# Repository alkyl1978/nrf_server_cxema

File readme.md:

печатная плата stelaris модуль с nrf24l01

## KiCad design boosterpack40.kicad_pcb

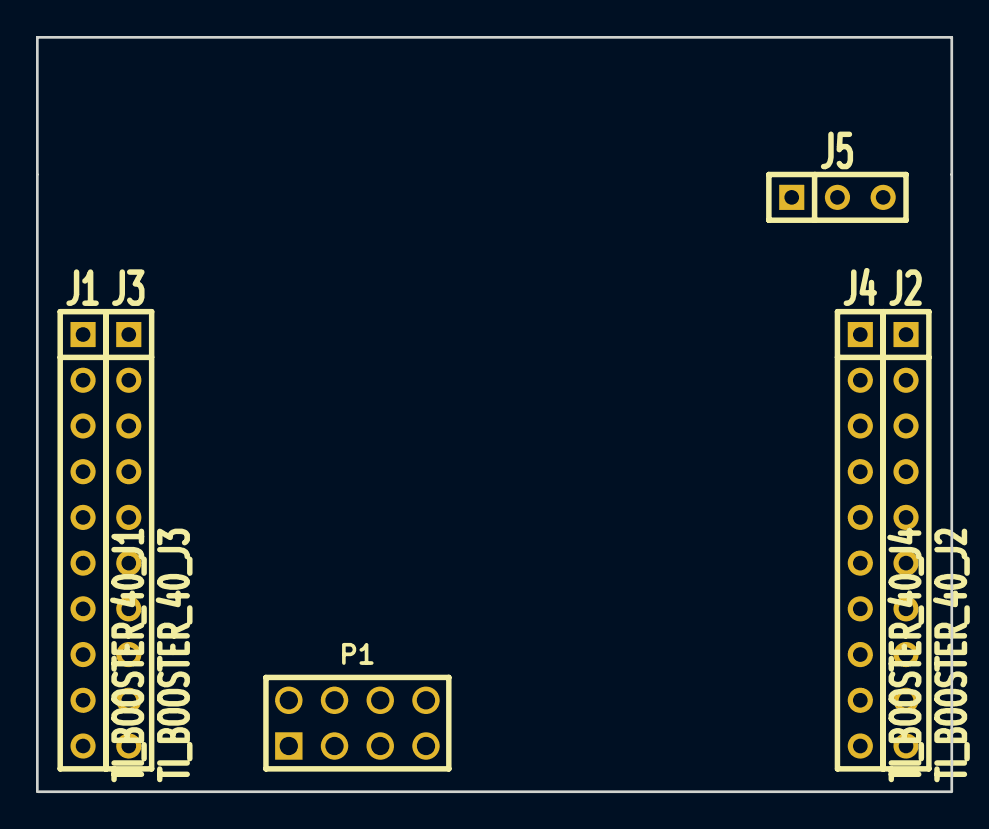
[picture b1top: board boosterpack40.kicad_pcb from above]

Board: 2 copper layers, 50.8 x 41.9 mm, 6 parts (0 on the bottom side), 2 nets, no tracks yet.

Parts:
J1: TI_BOOSTER_40_J1; SIL-10
J2: TI_BOOSTER_40_J2; SIL-10
J3: TI_BOOSTER_40_J3; SIL-10
J4: TI_BOOSTER_40_J4; SIL-10
J5: CONN_3; SIL-3
P1: NRF24L01 MODUL; pin_array_4x2

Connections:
GND: J2.1, J3.2, J5.2, J5.3, P1.1
VCC: J1.1, J5.1, P1.2

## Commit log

2015-11-22 first init
2015-11-22 добавлены документы
